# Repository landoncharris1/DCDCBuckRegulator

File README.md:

# DC-DC Buck Regulator
I will show how to implement a KiCad project for a 5V @ 1A DC-DC Buck Regulator using the TPS561208DDCR step-down converter.
This repo demonstrates:

Importing real-world components into KiCad (from Mouser via SamacSys Library Loader)

Creating a schematic with TPS561208DDCR, SPM3015T-4R7M, and 282834-2 connector

Laying out a PCB with low-EMI routing techniques

Generating a 3D model of the finished board

Understanding trace widths vs. current capacity

# Components Used
TPS561208DDCR – Synchronous step-down buck regulator

SPM3015T-4R7M – Power inductor (4.7 µH)

282834-2 – 2-pin connector for I/O

Passives (resistors & capacitors for feedback and filtering)

# 1) Importing Real Components from Mouser into KiCad
1. Download and install the SamacSys Library Loader, following the instructions:
 https://www.samacsys.com/kicad/

2. Configure the Library Loader to point to your KiCad library directory.

3. Search and download the following components from Mouser/SamacSys:

   282834-2 → Connector (TE Connectivity)
   TPS561208DDCR → Buck Regulator IC (Texas Instruments)
   SPM3015T-4R7M → Inductor (TDK)

4. The loader will automatically import schematic symbols, PCB footprints, and 3D models into KiCad.

# 2) Add Components in Schematic Editor 
1. Open KiCad → Schematic Editor.

2. Place components:

Add the 282834-2 connector at the input.
Place TPS561208DDCR as the main controller.
Add the SPM3015T-4R7M inductor to the regulator output stage.

3. Wire up supporting components (capacitors, resistors) per the datasheet reference design.

4. Run Electrical Rules Check (ERC) to confirm no missing connections.

# 3) Create PCB Layout in PCB Editor
1. Import the netlist into PCB Editor.

2. Place components close together (minimize high-current loop areas).

3. Route nets:

   Use wide traces for VIN, SW, OUT, and GND.
   Place GND fills/planes to reduce EMI.
   Use short traces for feedback and sensitive signals.

4. If traces must cross:

   Use a via (V key) to switch layers.
   Keep power traces thick, signal traces short.

5. Run DRC (Design Rule Check).

# 4) View the 3D Model
1. In PCB Editor, go to View → 3D Viewer.

2. Rotate and inspect the board:
Confirm imported models for 282834-2, TPS561208DDCR, and SPM3015T-4R7M are aligned properly.
Check component clearances.

3. Export STEP files for mechanical integration.

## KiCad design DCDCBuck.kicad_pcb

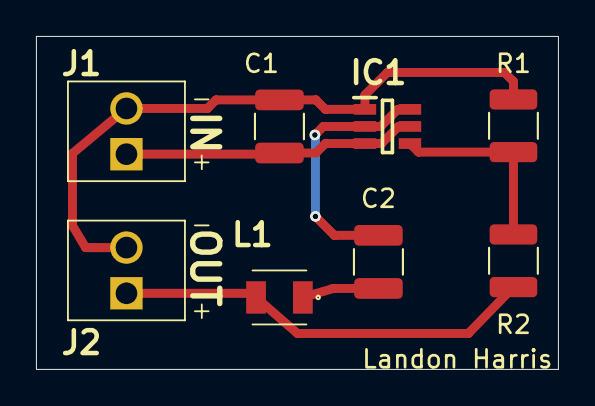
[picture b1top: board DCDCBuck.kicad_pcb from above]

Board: 2 copper layers, 29.0 x 18.5 mm, 8 parts (0 on the bottom side), 6 nets.

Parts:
C1: 22uF; C_1210_3225Metric
C2: 0.1uF; C_1210_3225Metric
IC1: TPS561208DDCR; SOT95P280X110-6N
J1, J2: IN; 282834-2_1
L1: SPM3015T-4R7M-LR; SPM3010-3020
R1: 10k; R_1210_3225Metric
R2: 56.2k; R_1210_3225Metric

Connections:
/IN: C1.1, IC1.3 (VIN), IC1.5 (EN), J1.1
/OUT: J2.1, L1.2, R2.1
GND: C1.2, IC1.1 (GND), J1.2, J2.2, R1.2
unnamed: C2.2, L1.1
unnamed: IC1.4 (VFB), R1.1, R2.2
VBST: C2.1, IC1.2 (SW), IC1.6 (VBST)
